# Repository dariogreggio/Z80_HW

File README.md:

# Z80_HW
an Emulator for the Z80 CPU, written in C and running on Microchip's PIC32.

Full boards have already been designed and tested; the new project is a little board, pin-compatible with Z80 CPU (40 pins DIL package)

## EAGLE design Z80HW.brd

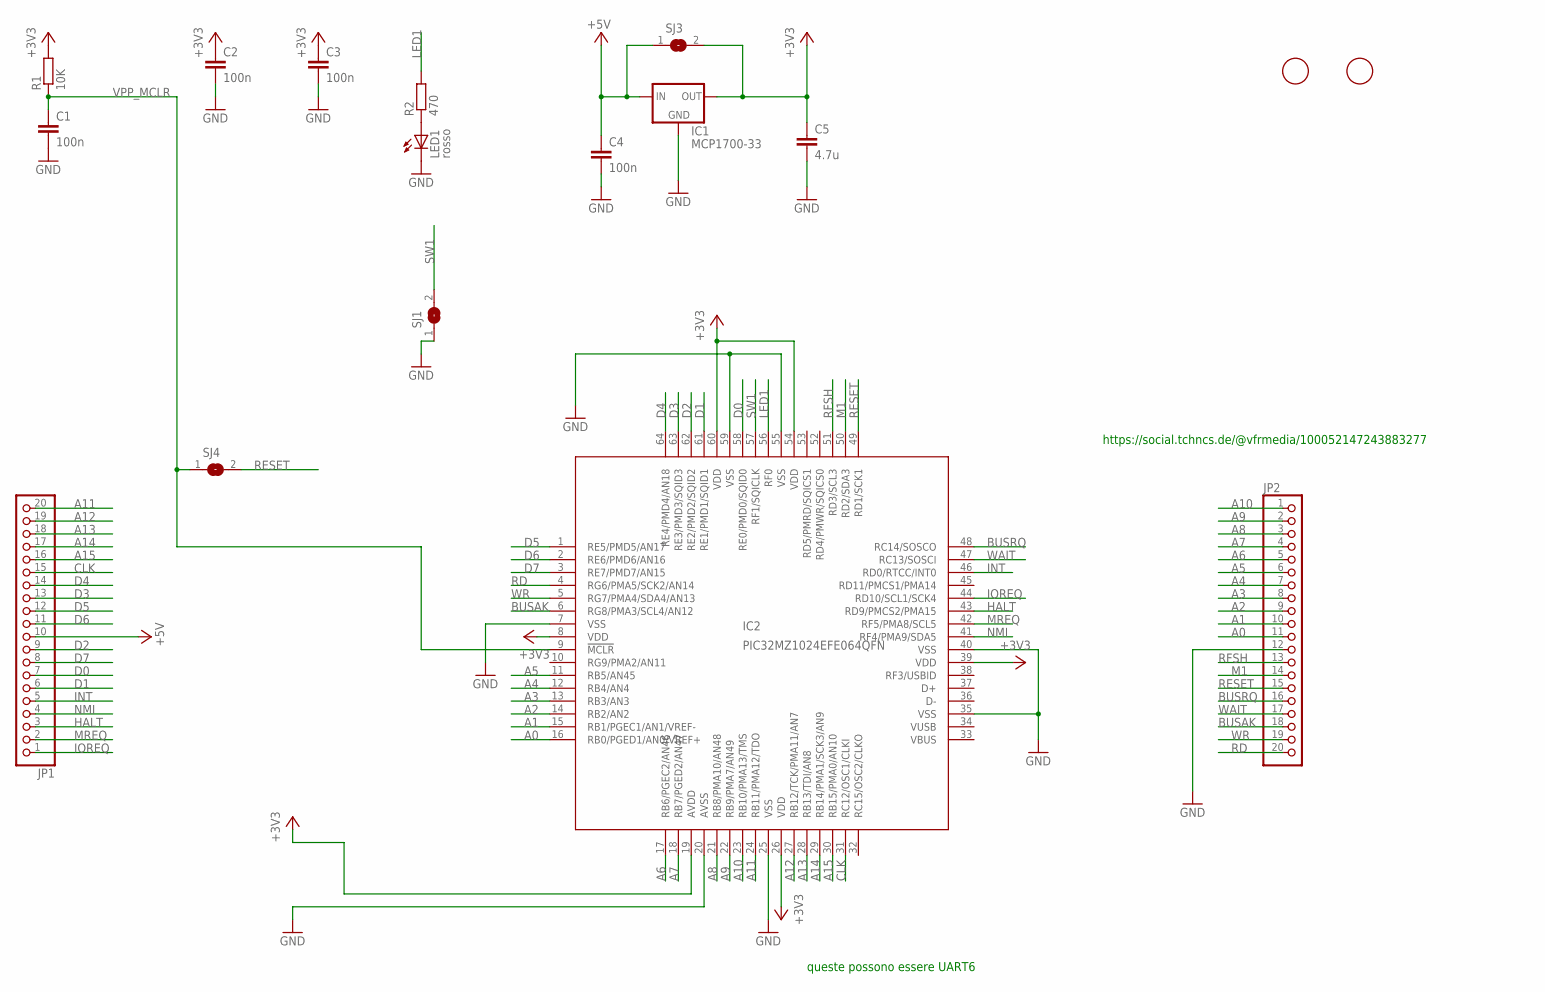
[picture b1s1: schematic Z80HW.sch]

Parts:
C1, C2, C3, C4: 100n; C0805
C5: 4.7u; C1206
F1, F2: FIDUCIAL; FIDUCIAL_1MM
IC1: MCP1700-33; SOT23
IC2: PIC32MZ1024EFE064QFN; QFN64
JP1, JP2: PINHD-1X20_2.54; 1X20
LED1: rosso; CHIPLED_0805
R1: 10K; R0805
R2: 470; R0805
SJ1, SJ3, SJ4: SJ

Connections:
+3V3: C2.1, C3.1, C5.1, IC1.2 (OUT), IC2.8 (VDD), IC2.19 (AVDD), IC2.26 (VDD), IC2.39 (VDD), IC2.54 (VDD), IC2.60 (VDD), R1.2, SJ3.2
+5V: C4.1, IC1.3 (IN), JP1.10, SJ3.1
A0: IC2.16 (RB0/PGED1/AN0/VREF+), JP2.11
A1: IC2.15 (RB1/PGEC1/AN1/VREF-), JP2.10
A2: IC2.14 (RB2/AN2), JP2.9
A3: IC2.13 (RB3/AN3), JP2.8
A4: IC2.12 (RB4/AN4), JP2.7
A5: IC2.11 (RB5/AN45), JP2.6
A6: IC2.17 (RB6/PGEC2/AN46), JP2.5
A7: IC2.18 (RB7/PGED2/AN47), JP2.4
A8: IC2.21 (RB8/PMA10/AN48), JP2.3
A9: IC2.22 (RB9/PMA7/AN49), JP2.2
A10: IC2.23 (RB10/PMA13/TMS), JP2.1
A11: IC2.24 (RB11/PMA12/TDO), JP1.20
A12: IC2.27 (RB12/TCK/PMA11/AN7), JP1.19
A13: IC2.28 (RB13/TDI/AN8), JP1.18
A14: IC2.29 (RB14/PMA1/SCK3/AN9), JP1.17
A15: IC2.30 (RB15/PMA0/AN10), JP1.16
BUSAK: IC2.6 (RG8/PMA3/SCL4/AN12), JP2.18
BUSRQ: IC2.48 (RC14/SOSCO), JP2.16
CLK: IC2.31 (RC12/OSC1/CLKI), JP1.15
D0: IC2.58 (RE0/PMD0/SQID0), JP1.7
D1: IC2.61 (RE1/PMD1/SQID1), JP1.6
D2: IC2.62 (RE2/PMD2/SQID2), JP1.9
D3: IC2.63 (RE3/PMD3/SQID3), JP1.13
D4: IC2.64 (RE4/PMD4/AN18), JP1.14
D5: IC2.1 (RE5/PMD5/AN17), JP1.12
D6: IC2.2 (RE6/PMD6/AN16), JP1.11
D7: IC2.3 (RE7/PMD7/AN15), JP1.8
GND: C1.2, C2.2, C3.2, C4.2, C5.2, IC1.1 (GND), IC2.7 (VSS), IC2.20 (AVSS), IC2.25 (VSS), IC2.35 (VSS), IC2.40 (VSS), IC2.55 (VSS), IC2.59 (VSS), JP2.12, LED1.C, SJ1.1
HALT: IC2.43 (RD9/PMCS2/PMA15), JP1.3
INT: IC2.46 (RD0/RTCC/INT0), JP1.5
IOREQ: IC2.44 (RD10/SCL1/SCK4), JP1.1
LED1: IC2.56 (RF0), R2.2
M1: IC2.50 (RD2/SDA3), JP2.14
MREQ: IC2.42 (RF5/PMA8/SCL5), JP1.2
unnamed: LED1.A, R2.1
NMI: IC2.41 (RF4/PMA9/SDA5), JP1.4
RD: IC2.4 (RG6/PMA5/SCK2/AN14), JP2.20
RESET: IC2.49 (RD1/SCK1), JP2.15, SJ4.2
RFSH: IC2.51 (RD3/SCL3), JP2.13
SW1: IC2.57 (RF1/SQICLK), SJ1.2
VPP_MCLR: C1.1, IC2.9 (!MCLR), R1.1, SJ4.1
VUSB: IC2.34 (VUSB)
WAIT: IC2.47 (RC13/SOSCI), JP2.17
WR: IC2.5 (RG7/PMA4/SDA4/AN13), JP2.19

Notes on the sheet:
queste possono essere UART6
https://social.tchncs.de/@vfrmedia/100052147243883277

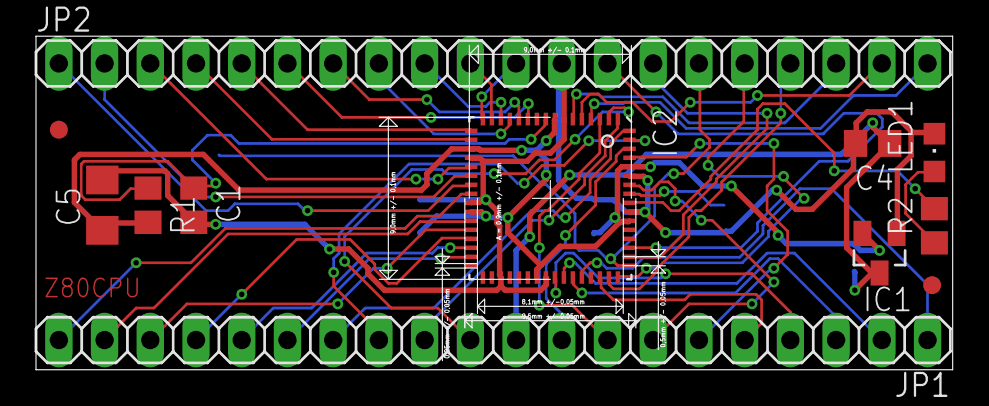
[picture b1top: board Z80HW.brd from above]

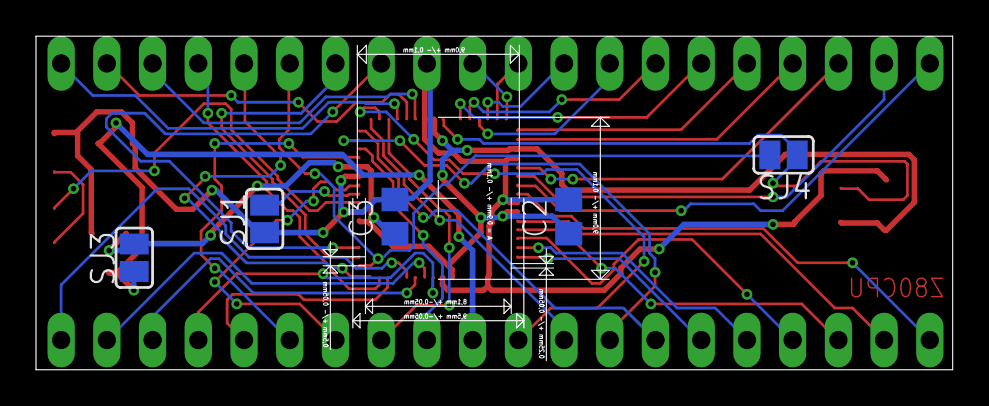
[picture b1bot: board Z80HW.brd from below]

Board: 2 copper layers, 50.9 x 18.5 mm, 17 parts (5 on the bottom side), 45 nets.

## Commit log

2022-03-09 Add files via upload
    PCB, version as of 9/3/2022 (1 route to go)
2022-03-09 Add files via upload
    finito!
